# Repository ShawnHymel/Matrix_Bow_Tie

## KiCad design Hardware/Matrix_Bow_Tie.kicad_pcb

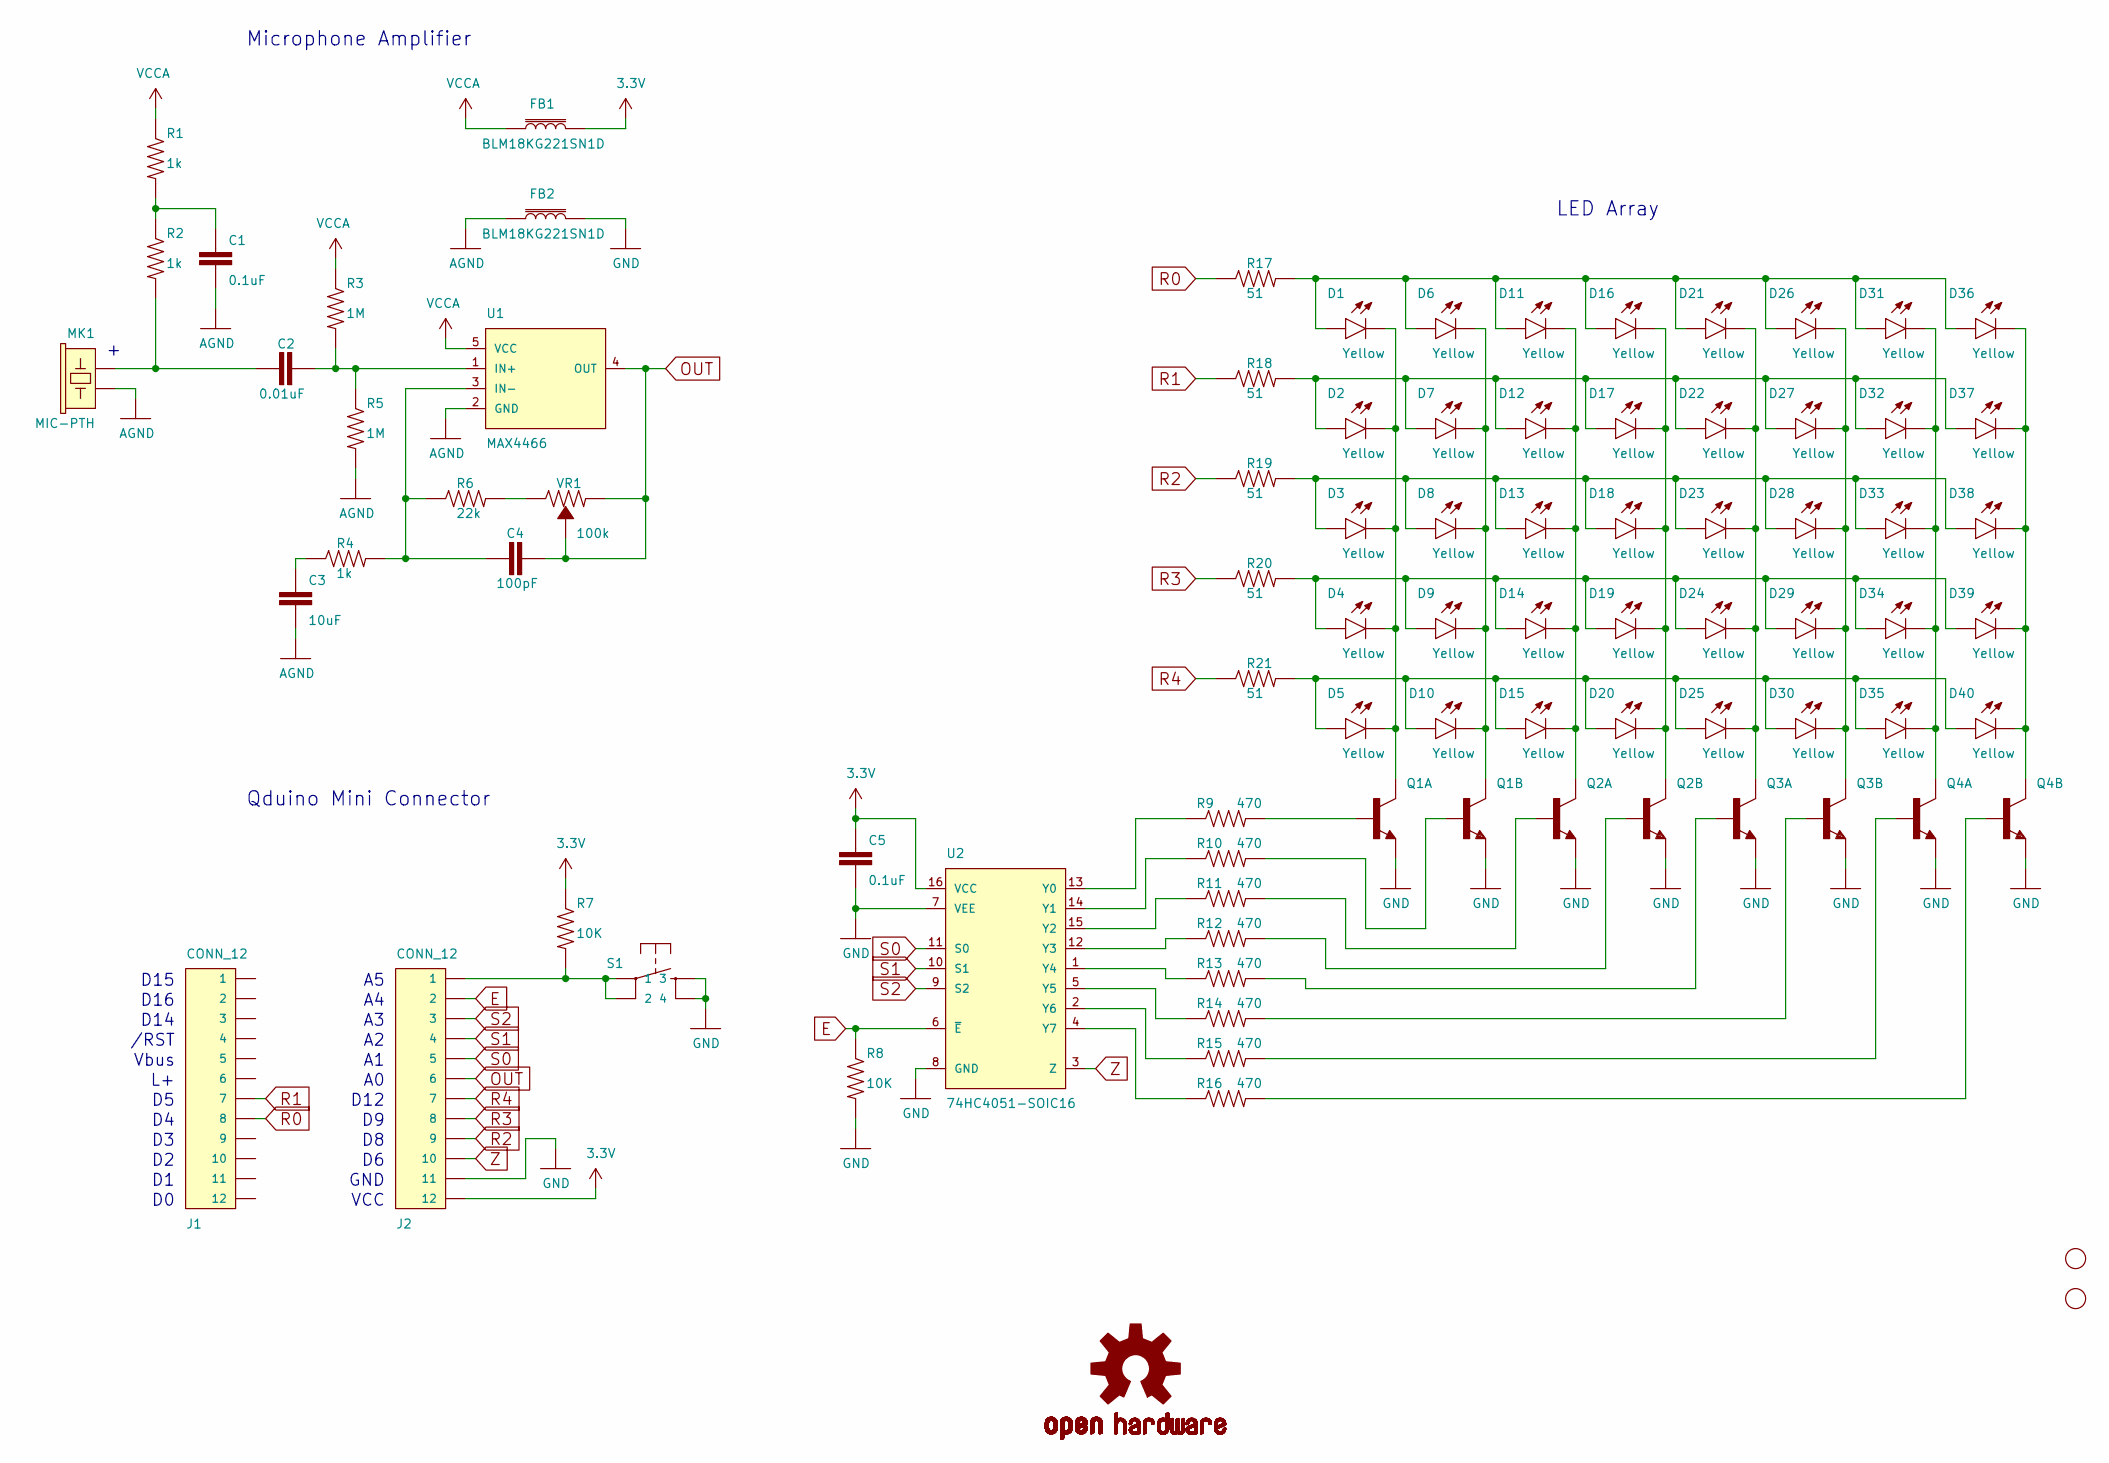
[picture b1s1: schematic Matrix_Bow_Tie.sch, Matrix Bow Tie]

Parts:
C1, C5: 0.1uF; 0603
C2: 0.01uF; 0603
C3: 10uF; 0805
C4: 100pF; 0603
D1, D2, D3, D4, D5, D6, D7, D8, D9, D10, D11, D12, D13, D14, D15, D16, D17, D18, D19, D20, D21, D22, D23, D24, D25, D26, D27, D28, D29, D30, D31, D32, D33, D34, D35, D36, D37, D38, D39, D40: Yellow; LED-0603
FB1, FB2: BLM18KG221SN1D; 0603
H1, H2: STAND-OFF
J1, J2: CONN_12; 1X12_SMD_MALE
LOGO1: OSHW-LOGOS; OSHW-LOGO-S
MK1: MIC-PTH; MICROPHONE-PTH-9.7MM
Q1, Q2, Q3, Q4: TRANS_NPN_DUAL-MBT3904DW1T1; SC70-6
R1, R2, R4: 1k; 0603
R3, R5: 1M; 0603
R6: 22k; 0603
R7, R8: 10K; 0603
R9, R10, R11, R12, R13, R14, R15, R16: 470; 0603
R17, R18, R19, R20, R21: 51; 0603
S1: MOMENTARY-SWITCH-SPST-2-SMD-4.6X2.8MM; TACTILE_SWITCH_SMD_4.6X2.8MM
U1: MAX4466; SC70-5
U2: 74HC4051-SOIC16; SOIC-16
VR1: 100k; TC33X

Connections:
3.3V: C5.1, FB1.2, J2.12, R7.1, U2.16 (VCC)
AGND: C1.2, C3.2, FB2.1, MK1.GND (2), R5.2, U1.2 (GND)
E: J2.2, R8.1, U2.6 (~E~)
GND: C5.2, FB2.2, J2.11, Q1.1 (E), Q1.4 (E), Q2.1 (E), Q2.4 (E), Q3.1 (E), Q3.4 (E), Q4.1 (E), Q4.4 (E), R8.2, S1.3, S1.4, U2.7 (VEE), U2.8 (GND)
unnamed: C1.1, R1.2, R2.1
unnamed: C2.1, MK1.OUT (1), R2.2
unnamed: C2.2, R3.2, R5.1, U1.1 (IN+)
unnamed: C3.1, R4.1
unnamed: C4.2, R4.2, R6.1, U1.3 (IN-)
unnamed: D1.A, D6.A, D11.A, D16.A, D21.A, D26.A, D31.A, D36.A, R17.2
unnamed: D1.C, D2.C, D3.C, D4.C, D5.C, Q1.3 (C)
unnamed: D5.A, D10.A, D15.A, D20.A, D25.A, D30.A, D35.A, D40.A, R21.2
unnamed: D6.C, D7.C, D8.C, D9.C, D10.C, Q1.6 (C)
unnamed: D11.C, D12.C, D13.C, D14.C, D15.C, Q2.3 (C)
unnamed: D2.A, D7.A, D12.A, D17.A, D22.A, D27.A, D32.A, D37.A, R18.2
unnamed: D3.A, D8.A, D13.A, D18.A, D23.A, D28.A, D33.A, D38.A, R19.2
unnamed: D4.A, D9.A, D14.A, D19.A, D24.A, D29.A, D34.A, D39.A, R20.2
unnamed: D16.C, D17.C, D18.C, D19.C, D20.C, Q2.6 (C)
unnamed: D21.C, D22.C, D23.C, D24.C, D25.C, Q3.3 (C)
unnamed: D26.C, D27.C, D28.C, D29.C, D30.C, Q3.6 (C)
unnamed: D31.C, D32.C, D33.C, D34.C, D35.C, Q4.3 (C)
unnamed: D36.C, D37.C, D38.C, D39.C, D40.C, Q4.6 (C)
unnamed: J2.1, R7.2, S1.1, S1.2
unnamed: Q1.2 (B), R10.2
unnamed: Q1.5 (B), R9.2
unnamed: Q2.2 (B), R12.2
unnamed: Q2.5 (B), R11.2
unnamed: Q3.2 (B), R14.2
unnamed: Q3.5 (B), R13.2
unnamed: Q4.2 (B), R16.2
unnamed: Q4.5 (B), R15.2
unnamed: R6.2, VR1.3 (CW)
unnamed: R9.1, U2.13 (Y0)
unnamed: R10.1, U2.14 (Y1)
unnamed: R11.1, U2.15 (Y2)
unnamed: R12.1, U2.12 (Y3)
unnamed: R13.1, U2.1 (Y4)
unnamed: R14.1, U2.5 (Y5)
unnamed: R15.1, U2.2 (Y6)
unnamed: R16.1, U2.4 (Y7)
OUT: C4.1, J2.6, U1.4 (OUT), VR1.1 (CCW), VR1.2 (WIPER)
R0: J1.8, R17.1
R1: J1.7, R18.1
R2: J2.9, R19.1
R3: J2.8, R20.1
R4: J2.7, R21.1
S0: J2.5, U2.11 (S0)
S1: J2.4, U2.10 (S1)
S2: J2.3, U2.9 (S2)
VCCA: FB1.1, R1.1, R3.1, U1.5 (VCC)
Z: J2.10, U2.3 (Z)

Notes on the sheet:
Microphone Amplifier
D15
D16
D14
/RST
Vbus
D12
GND
VCC
Qduino Mini Connector
LED Array

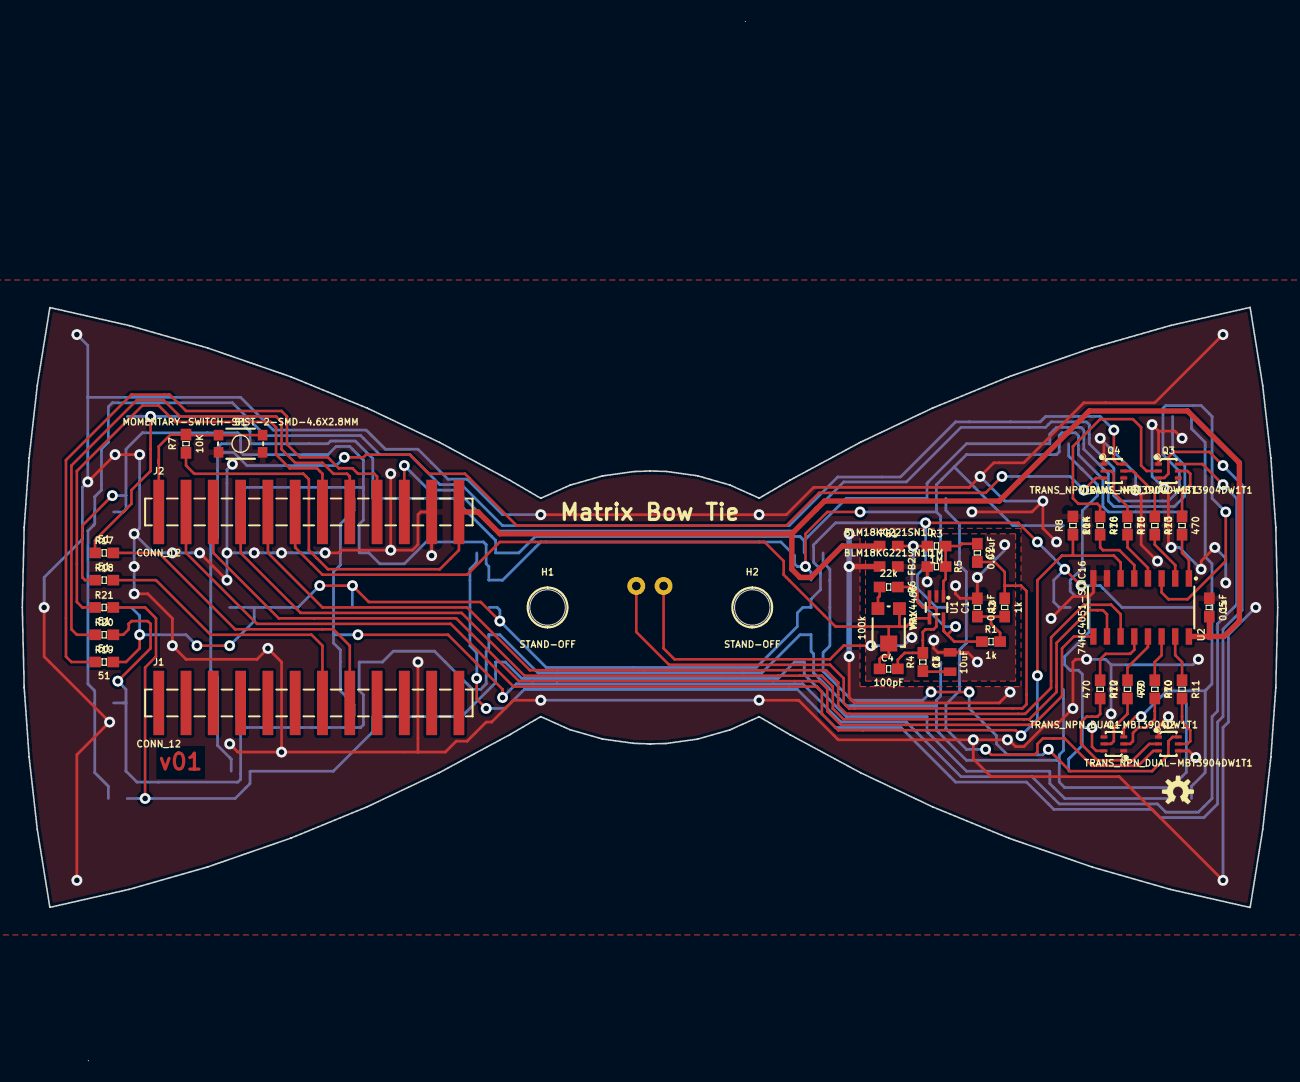
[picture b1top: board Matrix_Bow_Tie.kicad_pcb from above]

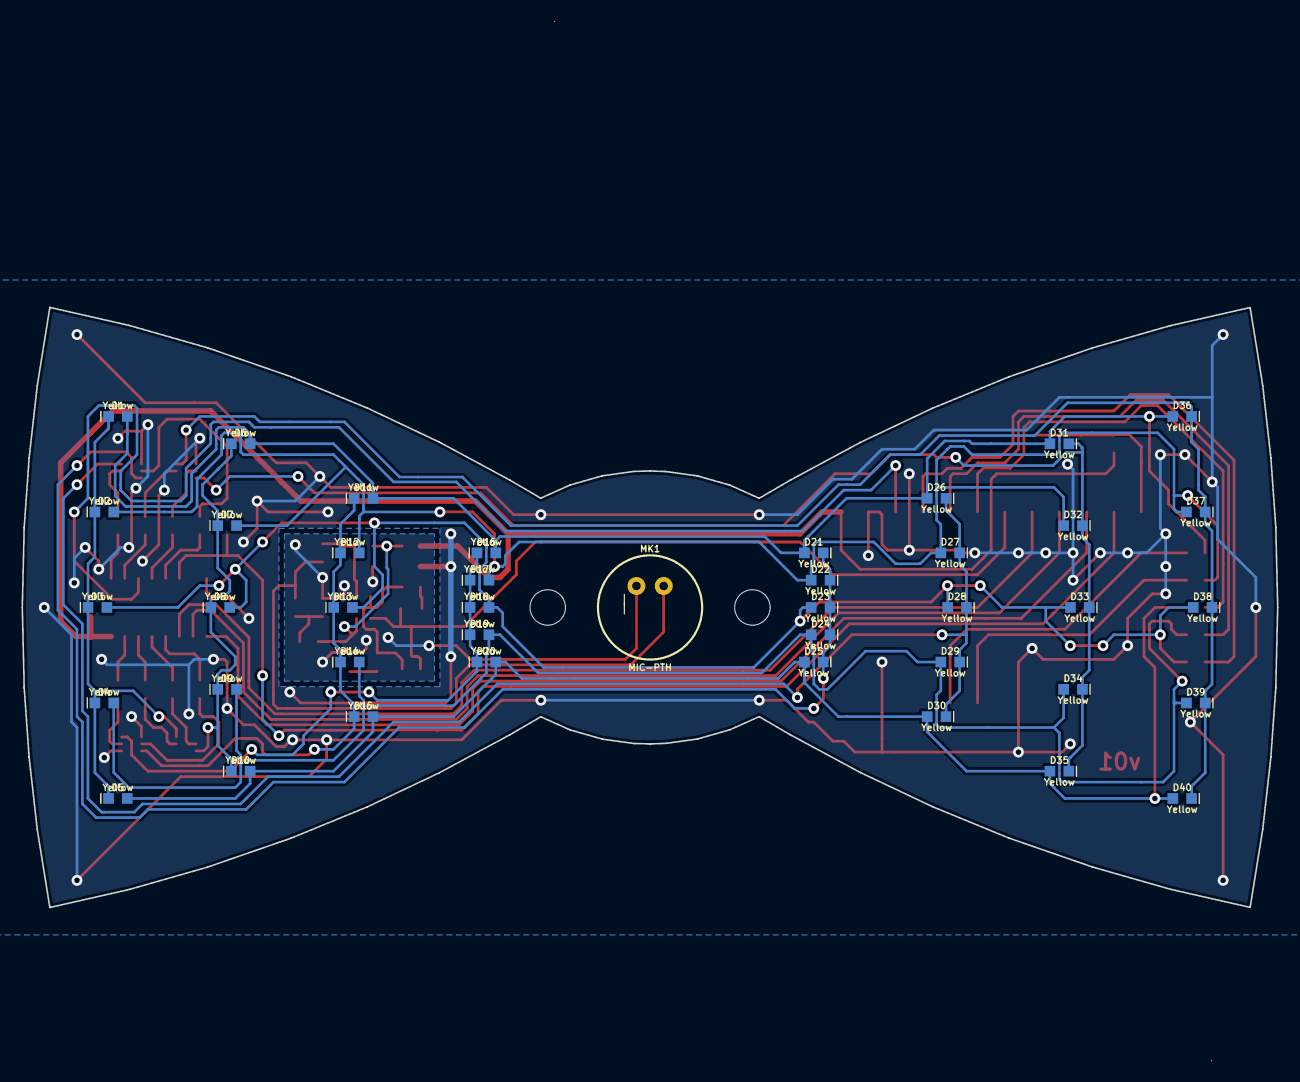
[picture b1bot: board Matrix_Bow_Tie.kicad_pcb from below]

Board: 2 copper layers, 116.9 x 96.6 mm, 82 parts (41 on the bottom side), 51 nets.

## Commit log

2017-09-03 Added MAX4466 part and SC70-5 footprint
2017-09-03 Added trimpot footprint and drew mic amp circuit.
2017-09-03 Removed backup files and added gitignore
2017-09-03 Removed link to unused rescure library
2017-09-09 Parts mostly laid out
2017-09-09 Added BOM
2017-09-09 More progress on layout
2017-09-10 Layout complete. Gerbers ran.
2017-09-10 Re-did copper pour. Magic happened. It fits the outline better now.

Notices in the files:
Hardware/Matrix_Bow_Tie.sch:
https://creativecommons.org/licenses/by-sa/4.0
Creative Commons Attribution Share-Alike 4.0 License
